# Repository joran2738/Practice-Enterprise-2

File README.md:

# Practice-Enterprise-2
Wij zijn Robin Van den Bergh en Joran Van Nieuwenhoven, twee studenten Embedded Software aan Thomas More.

Als project voor Practice Enterprise 2 hebben wij het maken van twee game consoles die zowel afzonderlijk als samen (tegen elkaar) konden spelen. De twee games die wij hebben ontworpen zijn ‘Space Invaders’ en ‘Brickbreakers’. De consoles bevatten naast een TFT-display en de mogelijkheid tot multiplayer ook een acceleratie sensor. Dit maakt het mogelijk om de spelletjes te spelen door de consoles te kantelen. Er is een micro-USB aansluiting voorzien om de console te voeden waardoor er gebruikt gemaakt kan worden van zowel een wall-adapter alsook bijvoorbeeld een powerbank.

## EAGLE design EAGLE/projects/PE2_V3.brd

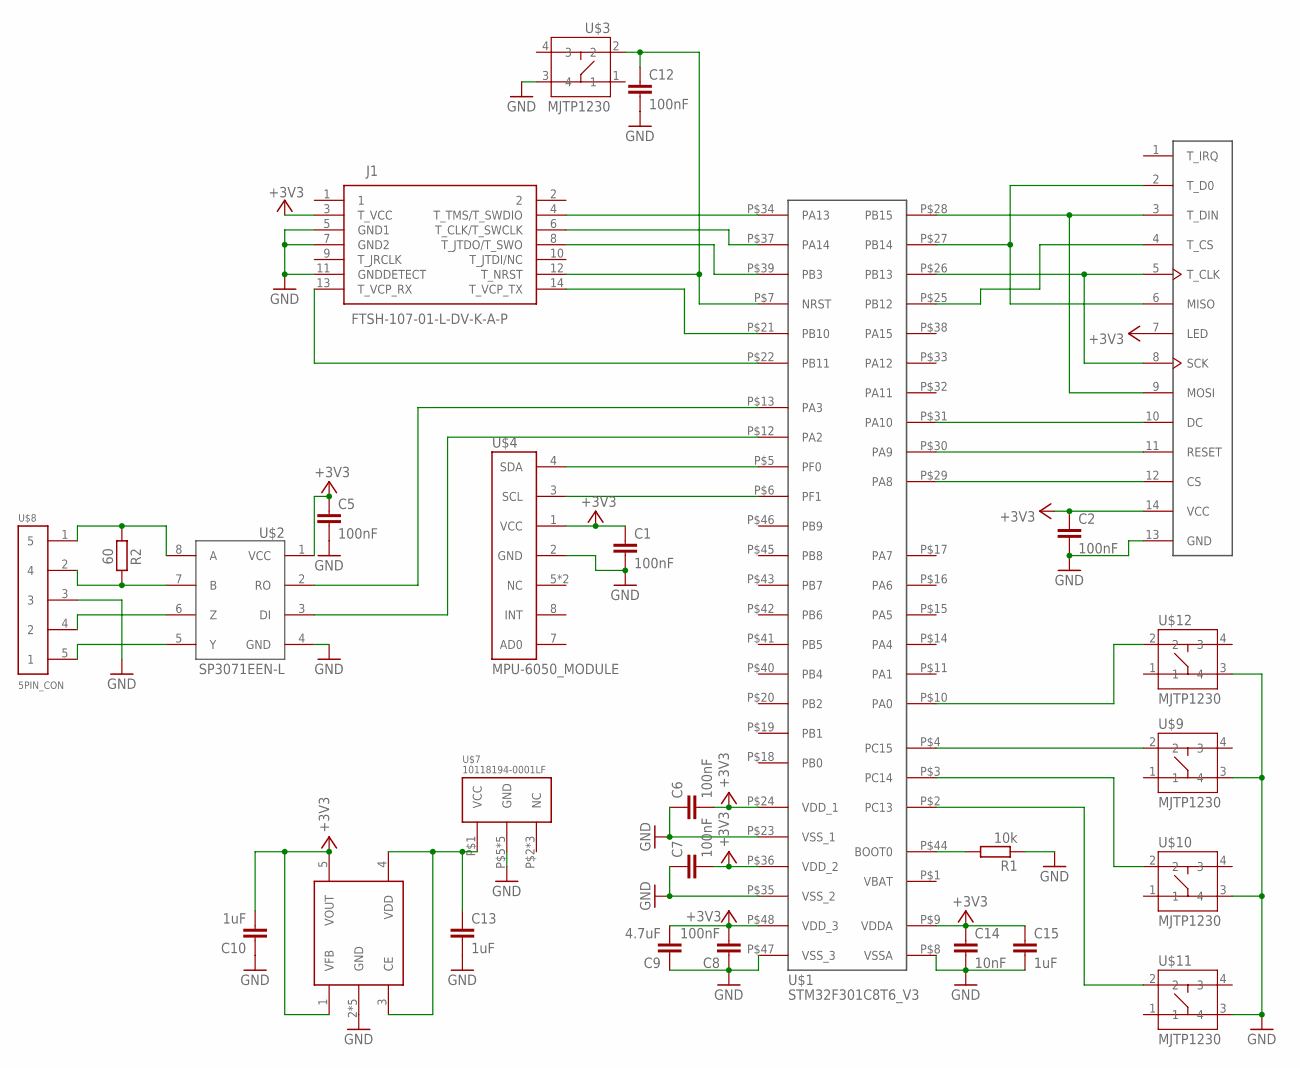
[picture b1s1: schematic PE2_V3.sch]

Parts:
C1, C2, C5, C6, C7, C8, C12: 100nF; C0805
C9: 4.7uF; C0805
C10, C13, C15: 1uF; C0805
C14: 10nF; C0805
J1: FTSH-107-01-L-DV-K-A-P; FTSH-107-XX-YYY-DV-K-A-P
R1: 10k; R0805
R2: 60; R0805
U$1: STM32F301C8T6_V3; STM32F301C8T6
U$2: SP3071EEN-L; SOIC127P600X175-8N
U$3, U$9, U$10, U$11, U$12: MJTP1230
U$4: MPU-6050_MODULE; HDRV8W64P254_1X8_2032X508X838B
U$5: SOT-89-5; SOT-89-5_TOR
U$6: 2.8_TFT_SPI_240X320_ILI8341; HDRV14W64P254_1X14_3556X508X838B
U$7: 10118194-0001LF
U$8: 5PIN_CON; HDRV5W64P254_1X5_1270X254X838B

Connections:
+3V3: C1.1, C2.1, C5.1, C6.2, C7.2, C8.2, C9.2, C10.2, C14.1, C15.1, J1.3 (T_VCC), U$1.P$9 (VDDA), U$1.P$24 (VDD_1), U$1.P$36 (VDD_2), U$1.P$48 (VDD_3), U$2.1 (VCC), U$4.1 (VCC), U$5.1 (VFB), U$5.5 (VOUT), U$6.7 (LED), U$6.14 (VCC)
GND: C1.2, C2.2, C5.2, C6.1, C7.1, C8.1, C9.1, C10.1, C12.2, C13.2, C14.2, C15.2, J1.5 (GND1), J1.7 (GND2), J1.11 (GNDDETECT), R1.1, U$1.P$8 (VSSA), U$1.P$23 (VSS_1), U$1.P$35 (VSS_2), U$1.P$47 (VSS_3), U$2.4 (GND), U$3.3 (4), U$4.2 (GND), U$5.2 (GND), U$5.6 (GND), U$5.P$1 (GND), U$5.P$2 (GND), U$5.P$3 (GND), U$6.13 (GND), U$7.P$5 (GND), U$7.P$6 (GND), U$7.P$7 (GND), U$7.P$8 (GND), U$7.P$9 (GND), U$8.3, U$9.3 (4), U$10.3 (4), U$11.3 (4), U$12.3 (4)
unnamed: J1.4 (T_TMS/T_SWDIO), U$1.P$34 (PA13)
unnamed: J1.6 (T_CLK/T_SWCLK), U$1.P$37 (PA14)
unnamed: J1.8 (T_JTDO/T_SWO), U$1.P$39 (PB3)
unnamed: C12.1, J1.12 (T_NRST), U$1.P$7 (NRST), U$3.2
unnamed: J1.14 (T_VCP_TX), U$1.P$21 (PB10)
unnamed: J1.13 (T_VCP_RX), U$1.P$22 (PB11)
unnamed: U$1.P$13 (PA3), U$2.2 (RO)
unnamed: U$1.P$5 (PF0), U$4.4 (SDA)
unnamed: U$1.P$12 (PA2), U$2.3 (DI)
unnamed: U$1.P$26 (PB13), U$6.5 (T_CLK), U$6.8 (SCK)
unnamed: U$1.P$28 (PB15), U$6.3 (T_DIN), U$6.9 (MOSI)
unnamed: U$1.P$25 (PB12), U$6.4 (T_CS)
unnamed: U$1.P$6 (PF1), U$4.3 (SCL)
unnamed: C13.1, U$5.3 (CE), U$5.4 (VDD), U$7.P$1 (VCC)
unnamed: R2.1, U$2.8 (A), U$8.1 (5)
unnamed: R2.2, U$2.7 (B), U$8.2 (4)
unnamed: U$2.6 (Z), U$8.4 (2)
unnamed: U$2.5 (Y), U$8.5 (1)
unnamed: U$1.P$27 (PB14), U$6.2 (T_D0), U$6.6 (MISO)
unnamed: U$1.P$29 (PA8), U$6.12 (CS)
unnamed: U$1.P$30 (PA9), U$6.11 (RESET)
unnamed: U$1.P$31 (PA10), U$6.10 (DC)
unnamed: U$1.P$4 (PC15), U$9.2
unnamed: U$1.P$10 (PA0), U$12.2
unnamed: U$1.P$3 (PC14), U$10.2
unnamed: U$1.P$2 (PC13), U$11.2
unnamed: R1.2, U$1.P$44 (BOOT0)

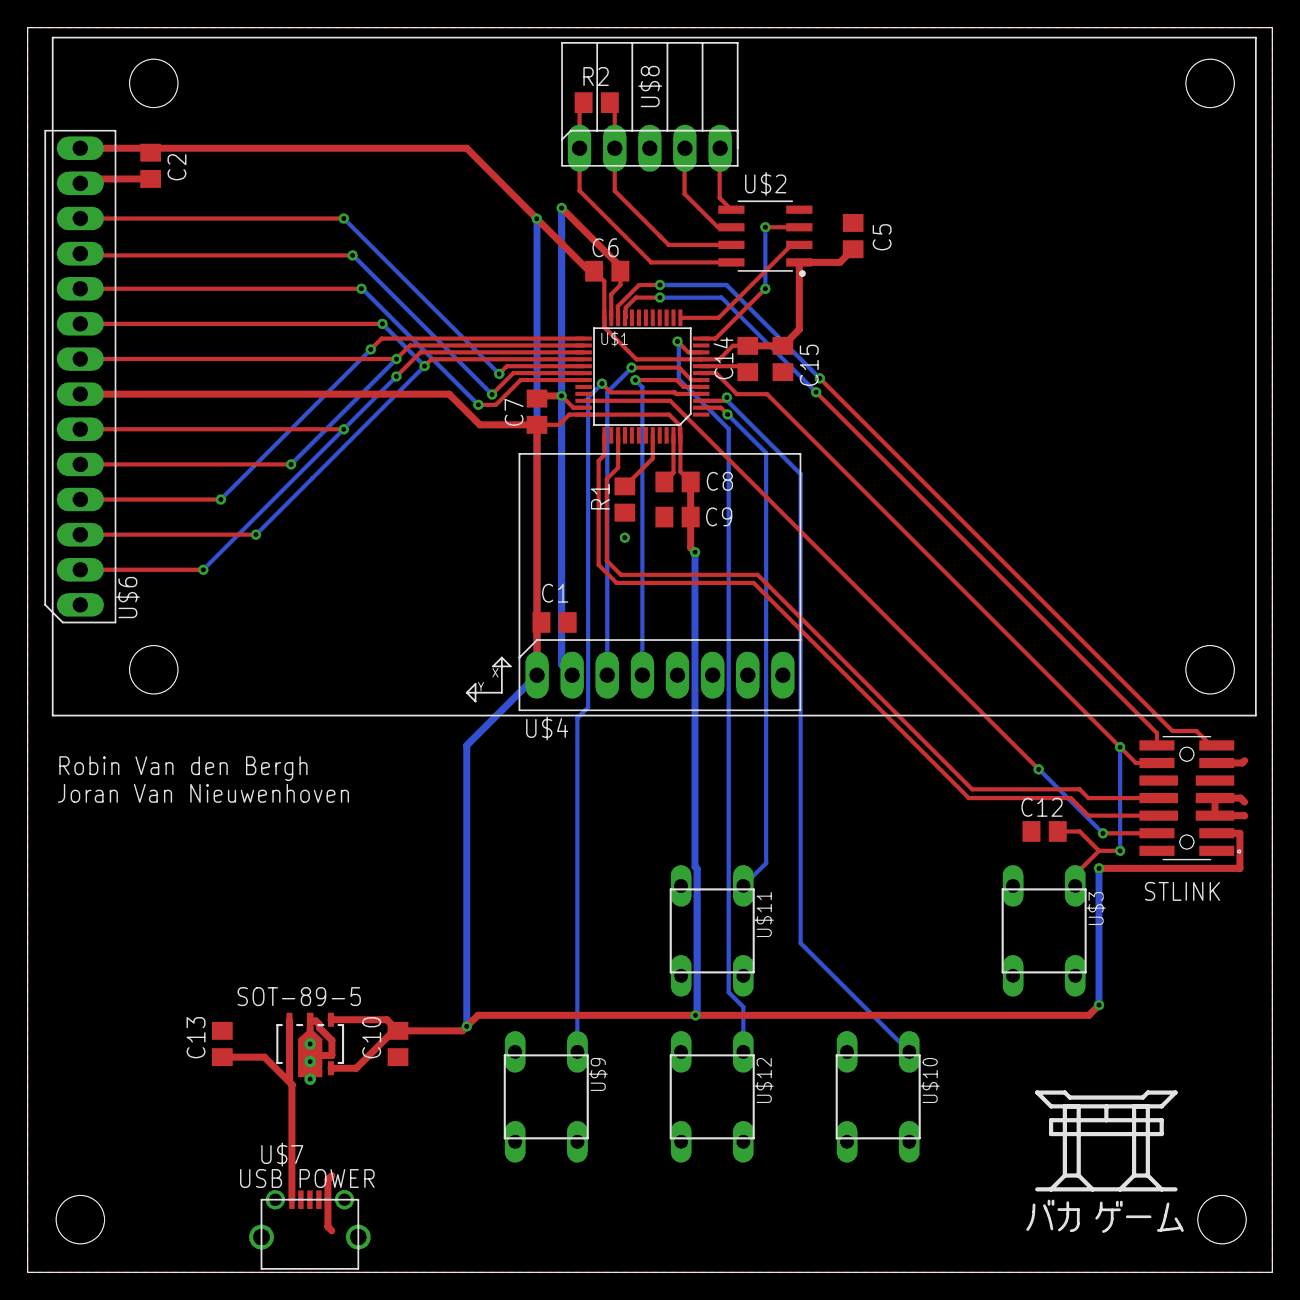
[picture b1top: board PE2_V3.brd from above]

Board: 2 copper layers, 90.0 x 90.0 mm, 27 parts (0 on the bottom side), 29 nets.

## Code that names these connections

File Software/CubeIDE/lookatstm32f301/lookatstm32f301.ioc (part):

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Mcu.Name=STM32F301C(6-8)Tx
Mcu.Package=LQFP48
Mcu.UserName=STM32F301C8Tx
PA0.GPIOParameters=GPIO_PuPd,GPIO_ModeDefaultEXTI
PA0.GPIO_ModeDefaultEXTI=GPIO_MODE_IT_FALLING
PA0.GPIO_PuPd=GPIO_PULLUP
PA0.Signal=GPXTI0
PA10.GPIOParameters=GPIO_Label
PA10.GPIO_Label=SPI2_DC
PA10.Signal=GPIO_Output
PA13.Mode=Trace_Asynchronous_SW
PA13.Signal=SYS_JTMS-SWDIO
PA14.Mode=Trace_Asynchronous_SW
PA14.Signal=SYS_JTCK-SWCLK
PA2.Mode=Asynchronous
PA2.Signal=USART2_TX
PA3.Mode=Asynchronous
PA3.Signal=USART2_RX
PA8.GPIOParameters=GPIO_Label
PA8.GPIO_Label=SPI2_CS
PA8.Signal=GPIO_Output
PA9.GPIOParameters=GPIO_Label
PA9.GPIO_Label=SPI2_RESET
PA9.Signal=GPIO_Output
PB10.Mode=Asynchronous
PB10.Signal=USART3_TX
PB11.Mode=Asynchronous
PB11.Signal=USART3_RX
PB12.GPIOParameters=GPIO_Label
PB12.GPIO_Label=SPI2_T_CS
PB12.Signal=GPIO_Output
PB13.Mode=Full_Duplex_Master
PB13.Signal=SPI2_SCK
PB14.Mode=Full_Duplex_Master
PB14.Signal=SPI2_MISO
PB15.Mode=Full_Duplex_Master
PB15.Signal=SPI2_MOSI
PB3.Mode=Trace_Asynchronous_SW
PB3.Signal=SYS_JTDO-TRACESWO
PC13.GPIOParameters=GPIO_PuPd,GPIO_ModeDefaultEXTI
PC13.GPIO_ModeDefaultEXTI=GPIO_MODE_IT_FALLING
PC13.GPIO_PuPd=GPIO_PULLUP
PC13.Signal=GPXTI13
PC14\ -\ OSC32_IN.GPIOParameters=GPIO_PuPd,GPIO_ModeDefaultEXTI
PC14\ -\ OSC32_IN.GPIO_ModeDefaultEXTI=GPIO_MODE_IT_FALLING
PC14\ -\ OSC32_IN.GPIO_PuPd=GPIO_PULLUP
PC14\ -\ OSC32_IN.Signal=GPXTI14
PC15\ -\ OSC32_OUT.GPIOParameters=GPIO_PuPd,GPIO_ModeDefaultEXTI
PC15\ -\ OSC32_OUT.GPIO_ModeDefaultEXTI=GPIO_MODE_IT_FALLING
PC15\ -\ OSC32_OUT.GPIO_PuPd=GPIO_PULLUP
PC15\ -\ OSC32_OUT.Signal=GPXTI15
PF0-OSC_IN.Mode=I2C
PF0-OSC_IN.Signal=I2C2_SDA
PF1-OSC_OUT.Mode=I2C
PF1-OSC_OUT.Signal=I2C2_SCL
RCC.HSEPLLFreq_Value=8000000
RCC.HSE_VALUE=8000000
RCC.SYSCLKFreq_VALUE=8000000
board=custom

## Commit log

2024-01-26 to do list
2024-01-31 added datasheets
2024-01-31 MPU research
2024-02-01 MPU-6000 edit
2024-02-01 starting on project proposal
2024-02-05 add already made libs and project files
2024-02-08 STMLINK header for PCB
2024-02-14 Added Gantt - Chart
2024-02-14 final touches before uploading
2024-02-15 Added library for regulator
2024-02-15 Added sheets for TFT screen
2024-02-15 Removed wrong sheets for TFT
2024-02-22 Added doc for useful link
2024-02-22 ORDER
2024-02-22 Added link for gyroscope module
2024-02-25 Added Qt Game Application Example
2024-03-02 added brd, some changes to sch aswell
2024-03-05 Started on pong
2024-03-07 Added simple brick function
    Added simplified 1 line bricks
2024-03-07 Added seperate functions for moving and changing directions
    Not yet fully implemented
2024-03-07 Did lots of things
    Started on two dimensional arrays for bricks, added ideeën files
2024-03-07 minor changes
2024-03-07 spaceinvadors
2024-03-07 got rid of code from brickbraker that's not need for spaceinvaders
2024-03-07 pewpew
    added a spaceship that can be controlled left to right, shoots ammo with spacebar
2024-03-13 Updated to latest Qt version
2024-03-13 Solved compatibility problems space invaders & brickbreakers (hopefully)
2024-03-13 Commit before merge
2024-03-14 Implemented brick collision
2024-03-14 Implemented life system
2024-03-14 Added moving bricks
2024-03-14 Added font header
2024-03-21 Added score (it's huge!)
2024-03-21 Did stuff
2024-03-21 gameu, spaceinvaders
2024-03-21 Added displayText.h
2024-03-21 Added defines for colors
2024-03-22 Moved displayText to displayText.c
2024-03-27 Added starting project for Pong
2024-03-27 Removed code concerning bricks in Pong
2024-03-27 Removed if statement for bricks
2024-03-27 Added Starting project for Snake
2024-03-27 Added border support
2024-03-27 Added life to bot
2024-03-27 Made bot unbeatable (or should be)
2024-03-27 Fixed bug where ball smashes through bricks
    fucking finally
2024-03-28 Made some minor changes to the bot + added score
2024-03-28 Added corner bounce
2024-03-28 Added power up: guardian barrier
2024-03-28 Added brick toughness
2024-03-28 menu
2024-04-04 menu
    cleared game.cpp so that it only has to call functions in spaceInvaders.h, added crude main menu functionality
2024-04-07 PCB design
    almost finished, just needs a check
2024-04-17 Created seperate .h and .c file for brickbreaker game
2024-04-17 added multiplayer and main menu
2024-04-18 Seperated brickbreaker code from game code
2024-04-18 Moved guardian timer
2024-04-25 Spaghetti
2024-04-25 Combined brickbreakers & menu & space invaders
2024-04-28 changes from 2 weeks ago
    V3 is the PCB layout that has been ordered
2024-04-28 cubeIDE code setup
2024-05-01 MPU-6050 can be read,
    raw data has not been converted to angles yet, complex math
2024-05-02 angle correct
    the angle still overshoots a bit, but it levels out, going right or left now is just with going further than 20° in each direction
2024-05-02 Added library for screen and implemented MPU6040 code
2024-05-06 PE2_V2
    things done:
    RAM was overflowed by 300kBytes, changed game_screen array to hold uint8_t numbers, representing colors, with a switch case these get converted when it needs to be written to the LCD
    this was not enough, in code the size of the screen is 4 times smaller, pixels in the game_screen array( 1 element) get converted to 4x4 pixels when written to the LCD
    menu''s work, spaceinvador works, tilt sensor as input works, but the screen still gets updated too slowly, we might have to not us the game_screen array but just update the things that have to be up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
2024-05-10 V3
    made the screen updating way faster, this was done by directly updating everything on it's own instead of first writing it to the game_screen array and writing this entire array to the screen everyti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
    started on some doxygen comments in spaceinvaders
2024-05-12 powerups
    added 2 powerups to spaceinvaders
    made some minor changes here and there
    button debouncing now works better
2024-05-12 added text
2024-05-16 Tested things with dma
2024-05-16 Added extra power
2024-05-16 Implemented brickbreakers
2024-05-16 Added brickbreakers ouleh
2024-05-16 fixed bug
2024-05-16 RANDOM macro was deleted, put it back
2024-05-18 changes to debug and game
    printf can now be used everywhere
    bug in game.c with pause menu
2024-05-19 Did things
2024-05-19 Added mp to V3
2024-05-23 Implemented more of mulitplayer
2024-05-23 Fixed some things
2024-05-23 start game multiplayer
2024-05-23 Added closing connection
2024-05-26 some comments
    doxygen comments added, some added to explain longer functions in spaceinvaders
    a point's coords need to be signed for spaceinvaders to work, changed this in common.h
2024-05-29 Added pause menu to multiplayer
2024-05-30 Redid some functions
2024-05-30 turned return functions in multiplayer to get functions (namewise)
2024-05-30 spaceinvaders bullet send to other console
    spaceinvaders now has the correct multiplayer implementation.
    changed the background of the pause menu and start text to a variable that can be set (borin has a different background than i do)
    the screen wasn't resetting from certain choices, e.g. the other console that receives a go back to menu just displayed the menu above the last state of the game, these are fixed
2024-05-31 Created seperate clearArray function
2024-06-01 cleaning up game.c and main.c
2024-06-01 Added doxygen to multiplayer and brickbreakers
2024-06-01 added text to the README
2024-06-02 Added connection lost support
2024-06-02 Updated BOM
2024-06-03 updated lives for space
